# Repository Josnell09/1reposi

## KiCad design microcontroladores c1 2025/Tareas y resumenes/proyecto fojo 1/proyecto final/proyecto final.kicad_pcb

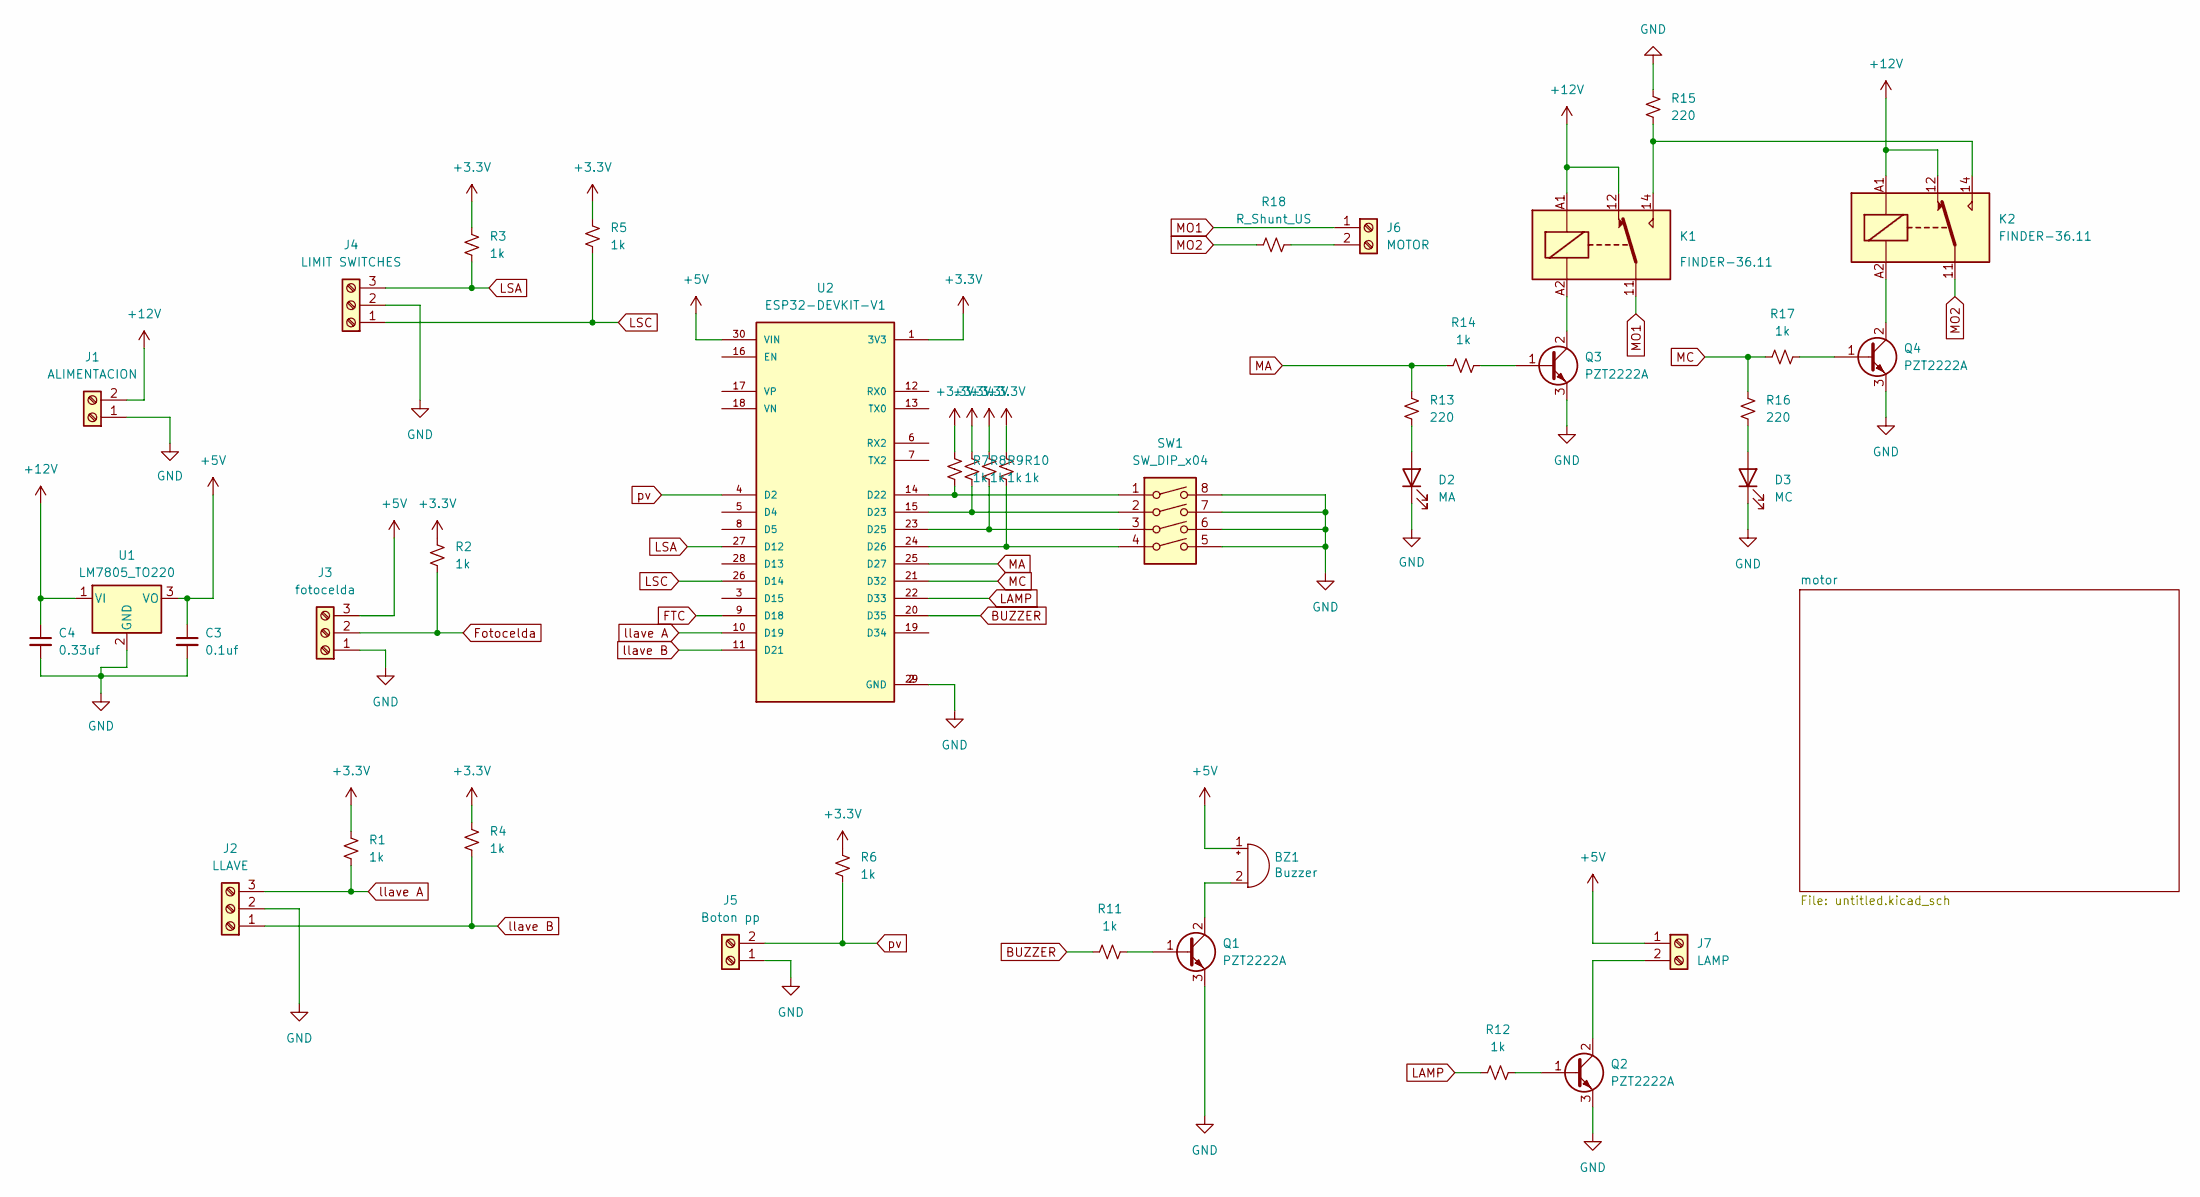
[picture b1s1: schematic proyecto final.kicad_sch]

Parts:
BZ1: Buzzer; Buzzer_CUI_CPT-9019S-SMT
C3: 0.1uf; C_0402_1005Metric
C4: 0.33uf; C_0402_1005Metric
D2: MA; LED_0402_1005Metric
D3: MC; LED_0402_1005Metric
J1: ALIMENTACION; TerminalBlock_bornier-2_P5.08mm
J2: LLAVE; TerminalBlock_bornier-3_P5.08mm
J3: fotocelda; TerminalBlock_bornier-3_P5.08mm
J4: LIMIT SWITCHES; TerminalBlock_bornier-3_P5.08mm
J5: Boton pp; TerminalBlock_bornier-2_P5.08mm
J6: MOTOR; TerminalBlock_bornier-2_P5.08mm
J7: LAMP; TerminalBlock_bornier-2_P5.08mm
K1, K2: FINDER-36.11; Relay_SPDT_Finder_36.11
Q1, Q2, Q3, Q4: PZT2222A; SOT-223-3_TabPin2
R1, R2, R3, R4, R5, R6, R7, R8, R9, R10, R11, R12, R14, R17: 1k; R_0402_1005Metric
R13, R15, R16: 220; R_0402_1005Metric
R18: R_Shunt_US; R_Shunt_Vishay_WSR2_WSR3
SW1: SW_DIP_x04; SW_DIP_SPSTx04_Slide_9.78x12.34mm_W8.61mm_P2.54mm
U1: LM7805_TO220; SOT-223
U2: ESP32-DEVKIT-V1; MODULE_ESP32_DEVKIT_V1; PARTREV N/A

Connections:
+3.3V: R1.1, R2.1, R3.1, R4.1, R5.1, R6.1, R7.1, R8.1, R9.1, R10.1, U2.1 (3V3)
+5V: BZ1.1 (+), C3.1, J3.3, J7.1, U1.3 (VO), U2.30 (VIN)
+12V: C4.1, J1.2, K1.12, K1.A1, K2.12, K2.A1, U1.1 (VI)
BUZZER: R11.1, U2.20 (D35)
FTC: U2.9 (D18)
Fotocelda: J3.2, R2.2
GND: C3.2, C4.2, D2.1 (K), D3.1 (K), J1.1, J2.2, J3.1, J4.2, J5.1, Q1.3 (E), Q2.3 (E), Q3.3 (E), Q4.3 (E), R15.1, SW1.5, SW1.6, SW1.7, SW1.8, U1.2 (GND), U2.2 (GND), U2.29 (GND)
LAMP: R12.1, U2.22 (D33)
LSA: J4.3, R3.2, U2.27 (D12)
LSC: J4.1, R5.2, U2.26 (D14)
MA: R13.2, R14.1, U2.25 (D27)
MC: R16.2, R17.1, U2.21 (D32)
MO1: J6.1, K1.11
MO2: K2.11, R18.2
unnamed: BZ1.2 (-), Q1.2 (C)
unnamed: D2.2 (A), R13.1
unnamed: D3.2 (A), R16.1
unnamed: J6.2, R18.1
unnamed: J7.2, Q2.2 (C)
unnamed: K1.14, K2.14, R15.2
unnamed: Q1.1 (B), R11.2
unnamed: Q2.1 (B), R12.2
unnamed: Q3.1 (B), R14.2
unnamed: K1.A2, Q3.2 (C)
unnamed: Q4.1 (B), R17.2
unnamed: K2.A2, Q4.2 (C)
unnamed: R7.2, SW1.1, U2.14 (D22)
unnamed: R8.2, SW1.2, U2.15 (D23)
unnamed: R9.2, SW1.3, U2.23 (D25)
unnamed: R10.2, SW1.4, U2.24 (D26)
llave A: J2.3, R1.2, U2.10 (D19)
llave B: J2.1, R4.2, U2.11 (D21)
pv: J5.2, R6.2, U2.4 (D2)

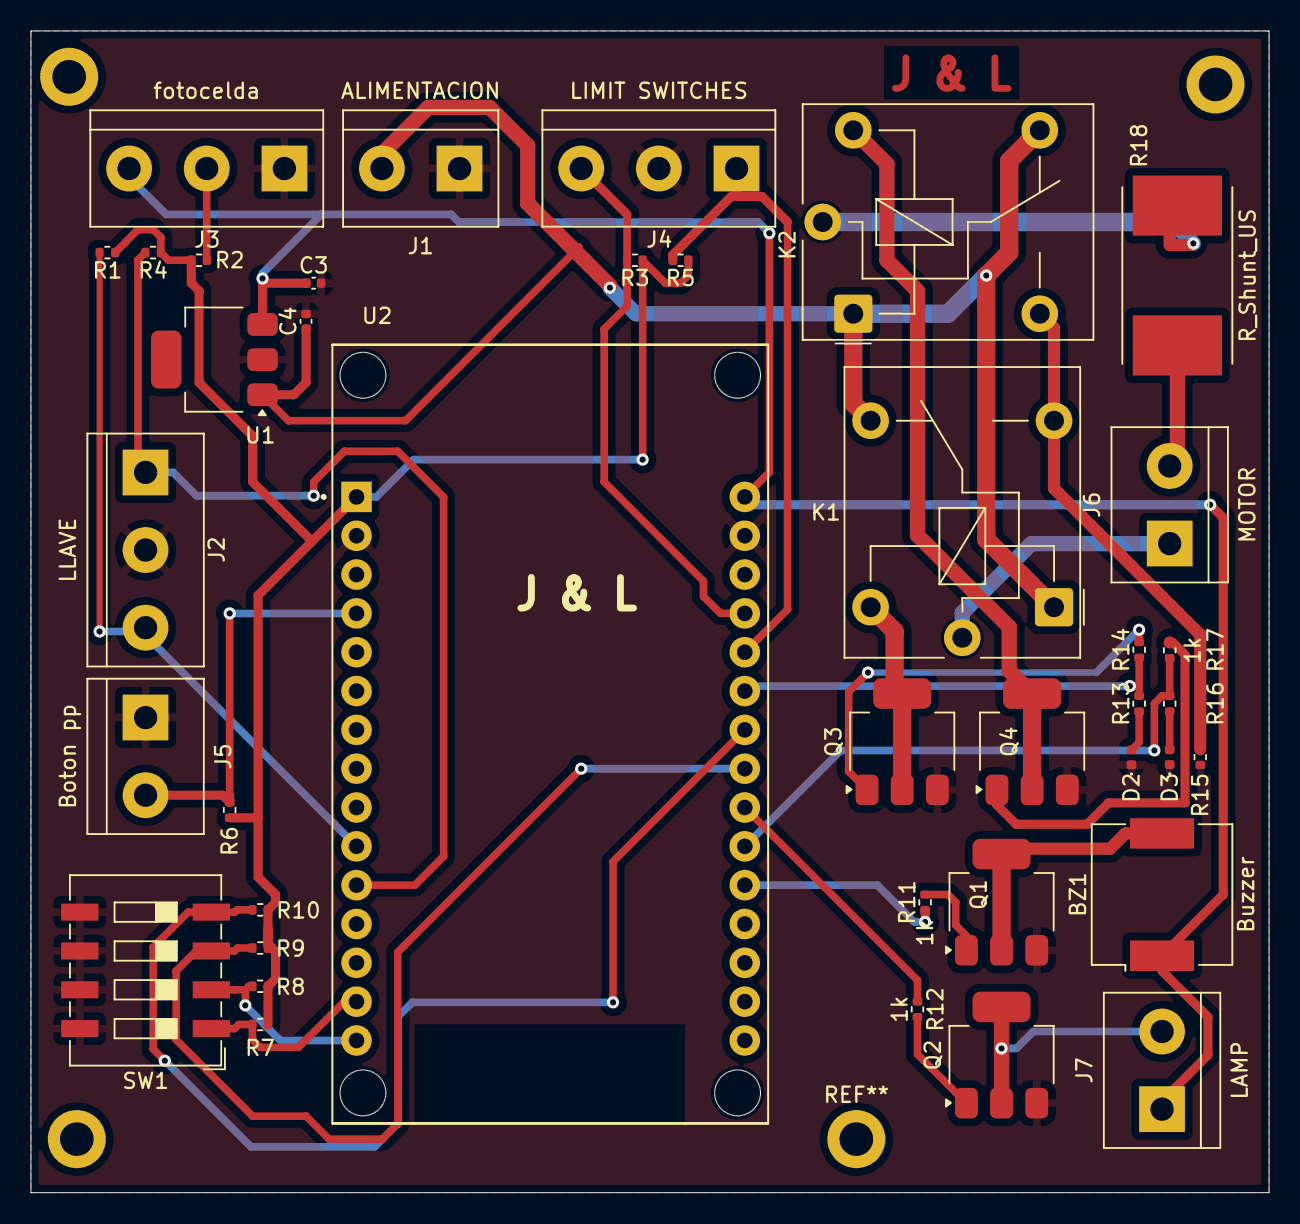
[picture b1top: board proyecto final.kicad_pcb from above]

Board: 2 copper layers, 81.0 x 76.0 mm, 39 parts (0 on the bottom side), 32 nets.

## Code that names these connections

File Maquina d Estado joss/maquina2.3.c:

#include <stdio.h>
#include <stdint.h>
#include <stdbool.h>
#include <unistd.h> // Para la función sleep()

// Definiciones de estados de la máquina
typedef enum {
    ESTADO_CERRADO,
    ESTADO_ABRIENDO,
    ESTADO_ABIERTO,
    ESTADO_CERRANDO,
    ESTADO_DETENIDA,
    ESTADO_DESCONOCIDO,
    ESTADO_ERROR
} ESTADO;

// Definiciones de pines y entradas
#define LSC  1  // Limit Switch Cerrado
#define LSA  2  // Limit Switch Abierto
#define FTC  3  // Fotocelda (sensor de obstrucción)
#define BTN_A  4  // Botón Abrir
#define BTN_C  5  // Botón Cerrar
#define BTN_PP 6  // Botón de Parada (Presencia)
#define DIP_MODE 7  // Configuración del modo (DIP Switch)

// Definiciones de salidas
#define MOTOR_A 8  // Motor Abriendo
#define MOTOR_C 9  // Motor Cerrando
#define LAMPARA 10 // Indicador luminoso

// Estructura para representar el estado de entradas/salidas
struct SYSTEM_IO {
    uint8_t lsc;
    uint8_t lsa;
    uint8_t ftc;
    uint8_t btn_a;
    uint8_t btn_c;
    uint8_t btn_pp;
    uint8_t dip_mode;
    uint8_t motor_a;
    uint8_t motor_c;
    uint8_t lampara;
} io;

// Estado actual
ESTADO estado_actual = ESTADO_CERRADO;

// Función de parpadeo de la lámpara en caso de error
void Timer50ms(void) {
    static unsigned int cnt_led_lamp = 0;
    cnt_led_lamp++;
    static bool led_state = false;
    if (estado_actual == ESTADO_ERROR) {
        if (cnt_led_lamp >= 10) { // Define la velocidad del parpadeo
            cnt_led_lamp = 0;
            led_state = !led_state;
            io.lampara = led_state;
        }
    } else {
        io.lampara = 0;
    }
}

// Función de actualización de estado
void actualizar_estado() {
    switch (estado_actual) {
        case ESTADO_CERRADO:
            if (io.btn_a) {
                estado_actual = ESTADO_ABRIENDO;
                io.motor_a = 1;
                io.motor_c = 0;
                printf("Transición: CERRADO -> ABRIENDO\n");
                sleep(4);
                estado_actual = ESTADO_ABIERTO;
                io.motor_a = 0;
                printf("Transición: ABRIENDO -> ABIERTO\n");
            }
            break;

        case ESTADO_ABIERTO:
            if (io.btn_c) {
                estado_actual = ESTADO_CERRANDO;
                io.motor_c = 1;
                io.motor_a = 0;
                printf("Transición: ABIERTO -> CERRANDO\n");
                sleep(4);
                estado_actual = ESTADO_CERRADO;
                io.motor_c = 0;
                printf("Transición: CERRANDO -> CERRADO\n");
            }
            break;

        case ESTADO_ABRIENDO:
        case ESTADO_CERRANDO:
            if (io.btn_pp) {
                estado_actual = ESTADO_DETENIDA;
                io.motor_a = 0;
                io.motor_c = 0;
                printf("Transición: DETENIDA\n");
            }
            break;

        case ESTADO_DETENIDA:
            if (io.btn_a) {
                estado_actual = ESTADO_ABRIENDO;
                io.motor_a = 1;
                printf("Reanudando apertura\n");
            } else if (io.btn_c) {
                estado_actual = ESTADO_CERRANDO;
                io.motor_c = 1;
                printf("Reanudando cierre\n");
            }
            break;

        case ESTADO_ERROR:
            io.motor_a = 0;
            io.motor_c = 0;
            printf("Sistema en estado de ERROR. Ingrese un comando válido para restaurar.\n");
            break;
    }
}

// Función para visualizar el estado y recibir comandos
void visualizar_estado() {
    printf("Estado actual: ");
    switch (estado_actual) {
        case ESTADO_CERRADO: printf("CERRADO\n"); break;
        case ESTADO_ABRIENDO: printf("ABRIENDO\n"); break;
        case ESTADO_ABIERTO: printf("ABIERTO\n"); break;
        case ESTADO_CERRANDO: printf("CERRANDO\n"); break;
        case ESTADO_DETENIDA: printf("DETENIDA\n"); break;
        case ESTADO_DESCONOCIDO: printf("DESCONOCIDO\n"); break;
        case ESTADO_ERROR: printf("ERROR\n"); break;
    }
    printf("Ingrese comando (a: abrir, c: cerrar, p: parar): ");
    char comando;
    scanf(" %c", &comando);

    if (comando == 'a') io.btn_a = 1;
    else if (comando == 'c') io.btn_c = 1;
    else if (comando == 'p') io.btn_pp = 1;
    else {
        printf("Comando inválido. Intente nuevamente.\n");
        estado_actual = ESTADO_ERROR;
    }

    if (estado_actual == ESTADO_ERROR && (comando == 'a' || comando == 'c' || comando == 'p')) {
        estado_actual = ESTADO_CERRADO;
        printf("Sistema restaurado.\n");
    }
}

int main() {
    while (1) {
        visualizar_estado();
        actualizar_estado();
        Timer50ms();
    }
    return 0;
}

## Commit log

2023-08-10 Create risxperrrrrrrpru
2023-08-10 Rename risxperrrrrrrpru to risxperrrrrrrpru.cs
2025-02-14 Add files via upload
    .c
